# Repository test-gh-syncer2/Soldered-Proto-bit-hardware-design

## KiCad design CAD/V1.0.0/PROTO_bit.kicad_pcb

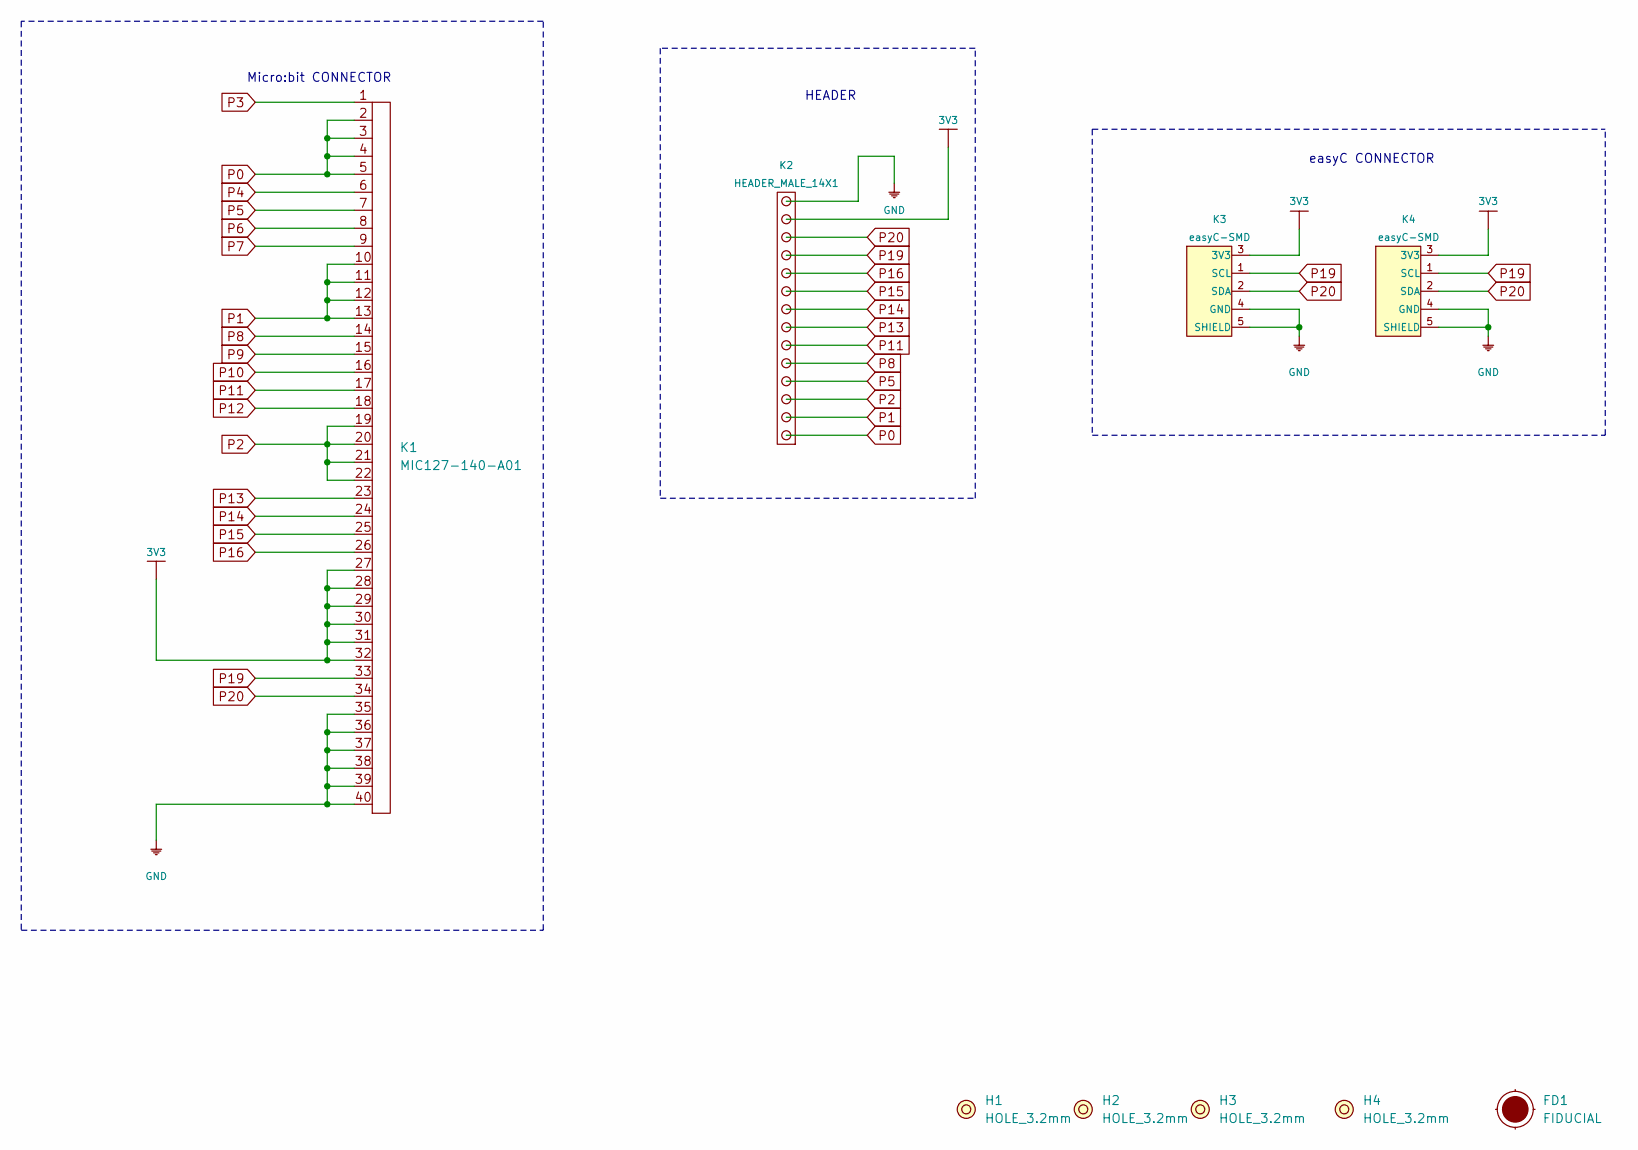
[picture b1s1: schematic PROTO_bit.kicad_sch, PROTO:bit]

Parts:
FD1: FIDUCIAL; FIDUCIAL_23
H1, H2, H3, H4: HOLE_3.2mm
K1: MIC127-140-A01; MC127-140-A01
K2: HEADER_MALE_14X1
K3, K4: easyC-SMD; easyC-connector

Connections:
3V3: K1.27, K1.28, K1.29, K1.30, K1.31, K1.32, K2.13, K3.3 (3V3), K4.3 (3V3)
GND: K1.35, K1.36, K1.37, K1.38, K1.39, K1.40, K2.14, K3.4 (GND), K3.5 (SHIELD), K4.4 (GND), K4.5 (SHIELD)
P0: K1.2, K1.3, K1.4, K1.5, K2.1
P1: K1.10, K1.11, K1.12, K1.13, K2.2
P2: K1.19, K1.20, K1.21, K1.22, K2.3
P3: K1.1
P4: K1.6
P5: K1.7, K2.4
P6: K1.8
P7: K1.9
P8: K1.14, K2.5
P9: K1.15
P10: K1.16
P11: K1.17, K2.6
P12: K1.18
P13: K1.23, K2.7
P14: K1.24, K2.8
P15: K1.25, K2.9
P16: K1.26, K2.10
P19: K1.33, K2.11, K3.1 (SCL), K4.1 (SCL)
P20: K1.34, K2.12, K3.2 (SDA), K4.2 (SDA)

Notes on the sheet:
Micro:bit CONNECTOR
HEADER
easyC CONNECTOR

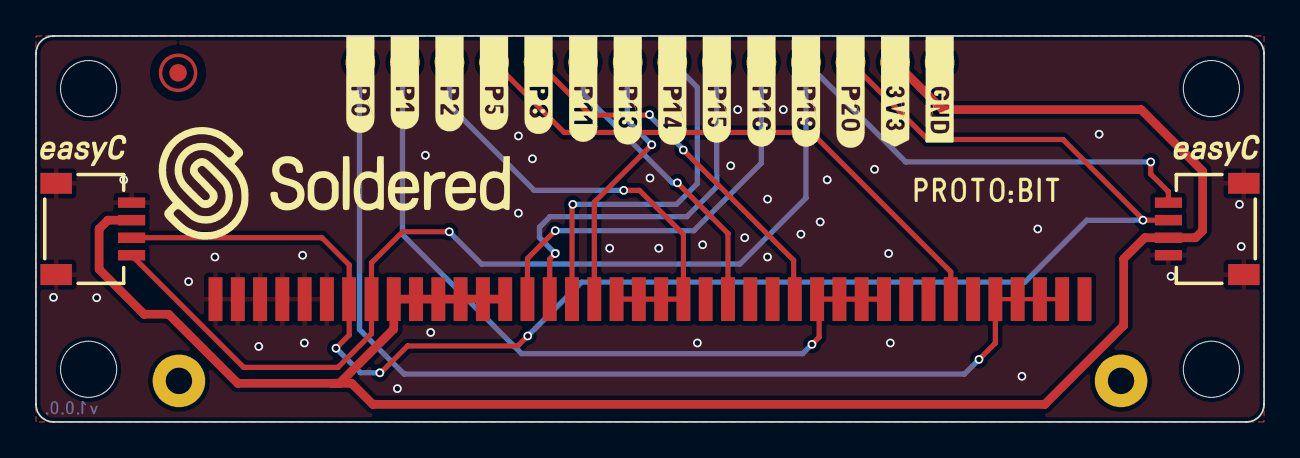
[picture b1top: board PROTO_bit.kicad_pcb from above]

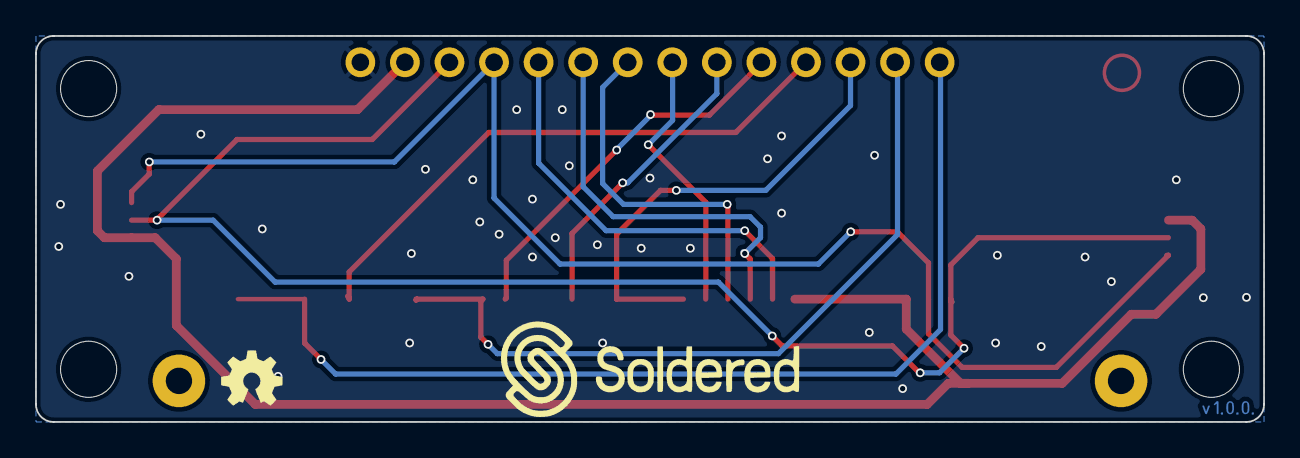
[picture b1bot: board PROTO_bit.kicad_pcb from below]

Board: 2 copper layers, 70.0 x 22.0 mm, 10 parts (2 on the bottom side), 14 nets.

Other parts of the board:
Ref**: Val**; Version1.0.0.

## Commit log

2021-09-23 Syncing to git
2021-09-23 Updating open source files.
